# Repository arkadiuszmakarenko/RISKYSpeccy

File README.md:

# RISKY Speccy

A CH32V307 RISC-V cartridge that plugs into the ZX Spectrum edge connector
and provides:

- **Snapshot loader** — load `.z80` v1/v2/v3 files from USB storage and
  launch them with full register restore.
- **Tape player** — play `.tap` / `.tzx` files by injecting the EAR signal
  directly onto the data bus, compatible with the Spectrum's built-in tape
  loader.
- **Interface 2 ROM cart** — load `.rom` / `.bin` files (up to 16 KB) as an
  Interface 2 style cartridge ROM, mapped into the Spectrum's 0x0000-0x3FFF
  region.
- **On-screen UI** — full-screen file browser and VT100-compatible terminal
  rendered by the CH32 onto the ZX screen via the NMI mailbox, without any
  Z80 cooperation.

See [docs/](docs/) for architecture and subsystem documentation.

---

## Repository layout

```
board/          KiCad schematic and PCB design
docs/           Architecture and subsystem documentation
firmware/       CH32 firmware source
  Core/         WCH RISC-V core support files
  Debug/        UART debug driver
  Ld/           Linker script
  Peripheral/   CH32V30x peripheral drivers
  Startup/      Startup assembly
  User/         Application code (main subsystems)
  zx_src/       Z80-side cart ROM firmware (SDCC)
Makefile        Root build file (builds everything)
```

---

## Building

### Prerequisites

**CH32 RISC-V toolchain** (WCH GCC 12):

Download from [MounRiver Studio](http://www.mounriver.com/) or extract the
standalone toolchain archive.  The default path expected by the Makefile is:

```
~/RISC-V_Embedded_GCC12
```

**Z80 toolchain** (for the `zx_src` sub-firmware):

```
sudo apt install sdcc
```

The `sdasz80` assembler is included with SDCC.  GNU `objcopy`, `od`, and
`awk` must also be available (standard on most Linux systems).

### Build

```sh
make
```

Override the toolchain path if needed:

```sh
make TOOLCHAIN_DIR=/path/to/RISC-V_Embedded_GCC12
```

Useful targets:

```sh
make help                # full list of targets
make build-all-versions  # bootloader + both app variants + combined image
make versions            # show all output artifact paths
make clean
```

Build outputs land in `build/`.

### Continuous integration (GitHub Actions)

A workflow at [`.github/workflows/build.yml`](.github/workflows/build.yml)
builds the firmware on every push, pull request, tag, and manual dispatch.
It:

- installs the WCH RISC-V toolchain (V2.10) and SDCC from `apt`
- runs `make` at the repo root
- verifies that all expected artifacts (`Bootloader.bin`, `RISKYSpeccy.bin`,
  `RISKYZXS.UPD`, `RISKYZXS_COMBINED.bin`) are produced
- checks that the bootloader and app-update binaries fit their respective
  flash regions
- uploads the binaries as a workflow artifact
  (`RISKYZXSpectrum-firmware`, retained for 90 days) and the listings/maps
  as a separate logs artifact
- on tag pushes (`v*`) and on `release` events, attaches the user-facing
  binaries (`*.bin` / `*.UPD` at the top of `build/`) to a GitHub Release

The default `latest` release is marked as prerelease and is updated on
every non-PR run; tagged builds (`v1.2.3`, etc.) become stable releases.
No secrets are required — the workflow uses the default `GITHUB_TOKEN`
to create/update releases.

### Flashing options

| Mode | Command | Output | When to use |
|------|---------|--------|-------------|
| **Combined** (default) | `make flash` | `build/RISKYZXS_COMBINED.bin` | Fresh cartridge setup or bootloader + app in one shot |
| **Standalone (no BL)** | `make flash-standalone` | `build/RISKYSpeccy.bin` | Development or single-firmware deployment |
| **Bootloader only** | `make flash-bootloader` | `build/bootloader/Bootloader.bin` | Bootloader maintenance / recovery |
| **App via USB** | _(copy to USB drive)_ | `build/RISKYZXS.UPD` | After bootloader is installed |

The Linux `make flash*` targets drive a **WCH-LinkE** via OpenOCD.

#### Programming on Windows with WCH tools

1. Install [WCHISPTool](https://www.wch.cn/downloads/WCHISPTool_Setup_exe.html)
   and the **WCH-LinkE** USB driver (WCH provides a signed INF/VCP driver
   bundle — let the installer do it, or grab the driver from the
   MounRiver Studio distribution).
2. Connect the **WCH-LinkE** to the cartridge's SWD header (SWDIO / SWCLK /
   GND).  Power the Spectrum so the CH32V307 is alive on the edge connector.
3. Launch **WCHISPTool** and pick the chip family **CH32V30x** (the
   CH32V307 lives in this group).
4. In the device list, select the WCH-LinkE you just plugged in.  The tool
   should show the chip's `Device ID` once it talks to the target.
5. Click **...** next to the file box and point it at the build output:
   - `build/RISKYZXS_COMBINED.bin` — bootloader + application in one shot
     (use the **.bin** image, not `.elf`/`.hex`)
   - `build/RISKYSpeccy.bin` — application only (no bootloader)
   - `build/bootloader/Bootloader.bin` — bootloader only
6. Set the start address to **`0x08000000`** for any of the above.
7. Enable **"Erase before program"** and **"Verify after program"**, then
   click **Download** (or press F5).  Progress shows in the status bar;
   "Success" means programming finished and verified.

#### Updating the application via USB (no programmer)

For the **app-via-USB** path, the bootloader must already be installed on
the cartridge (use the WCHISPTool flow above once with the combined or
bootloader image to put it in place).

1. Copy `build/RISKYZXS.UPD` to the **root** of a **FAT12/FAT16/FAT32**
   formatted USB drive.
2. Insert the USB drive into the cartridge's USB port.
3. To **force IAP mode** (e.g. if the application is wedged and you want
   to reflash), fit a jumper across the **SWDIO / SWCLK** header pins
   before powering on.
4. Power on (or reset) the cartridge. The Ready LED should flash 3 times.
   The bootloader detects the drive and programs the application. If
   programming was successful, the Ready LED will flash slowly 10 times.
   If unsuccessful, it will start rapidly flashing.

See [docs/bootloader.md](docs/bootloader.md) for the full update flow,
state-machine details, and recovery options.

---

## CH32V303 RAM / FLASH split

The CH32V303 lets you trade FLASH for RAM (or vice versa) via the
**SRAM_CODE_MODE** field — bits `[7:6]` of the USER option byte at
`0x1FFFF802`.  The four available splits are:

| SRAM_CODE_MODE | FLASH  | RAM    |
|----------------|--------|--------|
| `00`           | 192 KB | 128 KB |
| `01`           | 224 KB |  96 KB |
| `10`           | 256 KB |  64 KB |
| `11`           | 288 KB |  32 KB |

This project uses **`00`** (192 KB FLASH + 128 KB RAM).  **You must set
this split before flashing the firmware**, otherwise RAM and FLASH regions
will not match the linker script and the firmware will not run.

### Setting the split with WCHISPTool (recommended)

This is the easiest method and requires only the WCH-LinkE programmer.

1. Open **WCHISPTool**, select chip family **CH32V30x**, and connect to the
   target (same as for flashing firmware — see [Flashing options](#flashing-options)).
2. Switch to the **Config** (or **Option Byte**) tab.
3. Locate the **SRAM_CODE_MODE** field (labelled `USER[7:6]` in some
   versions).
4. Select **`00`** from the drop-down to configure 192 KB FLASH + 128 KB RAM.
5. Click **Program** (or **Download**) to write the option byte.
6. Power-cycle or reset the board.  The new split is now active and you can
   proceed to flash the firmware.

### Setting the split with the Makefile (Linux + WCH-LinkE)

The repository provides Makefile targets that set the split and reboot the
chip in one step.  This is the quickest path on Linux.

| Command | Description |
|---------|-------------|
| `make split-info` | Read current option bytes (uses `minichlink -i`) |
| `make split-set` | Set the split to `MODE=0` (192K FLASH + 128K RAM) via minichlink |
| `make split-set MODE=0 SPLIT_TOOL=openocd` | Same, but uses OpenOCD |
| `make split-set-minichlink MODE=N` | Set split via minichlink, `N` = 0..3 |
| `make split-set-openocd MODE=N` | Set split via OpenOCD, `N` = 0..3 |

`MODE` values: `0` = 192K FLASH + 128K RAM, `1` = 224K + 96K, `2` = 256K + 64K,
`3` = 288K + 32K.  **This project requires `MODE=0`.**

```sh
# Default (recommended): mode 0 via minichlink
make split-set

# Mode 0 via OpenOCD
make split-set SPLIT_TOOL=openocd

# Power-cycle the board, then flash firmware
make flash
```

> After writing, power-cycle the board before flashing firmware.

### Setting the split with OpenOCD / WCH-LinkE on Linux (manual)

```sh
openocd -f interface/wch-riscv.cfg \
        -c "init; halt; \
            flash write_word 0x1FFFF802 0xC03F; \
            reset; exit"
```

The half-word `0xC03F` encodes USER byte `0x3F` (`SRAM_CODE_MODE = 00`,
all other bits at default) in the low byte and its complement `0xC0` in
the high byte, as required by the option byte format.

> After writing, power-cycle the board before flashing firmware.

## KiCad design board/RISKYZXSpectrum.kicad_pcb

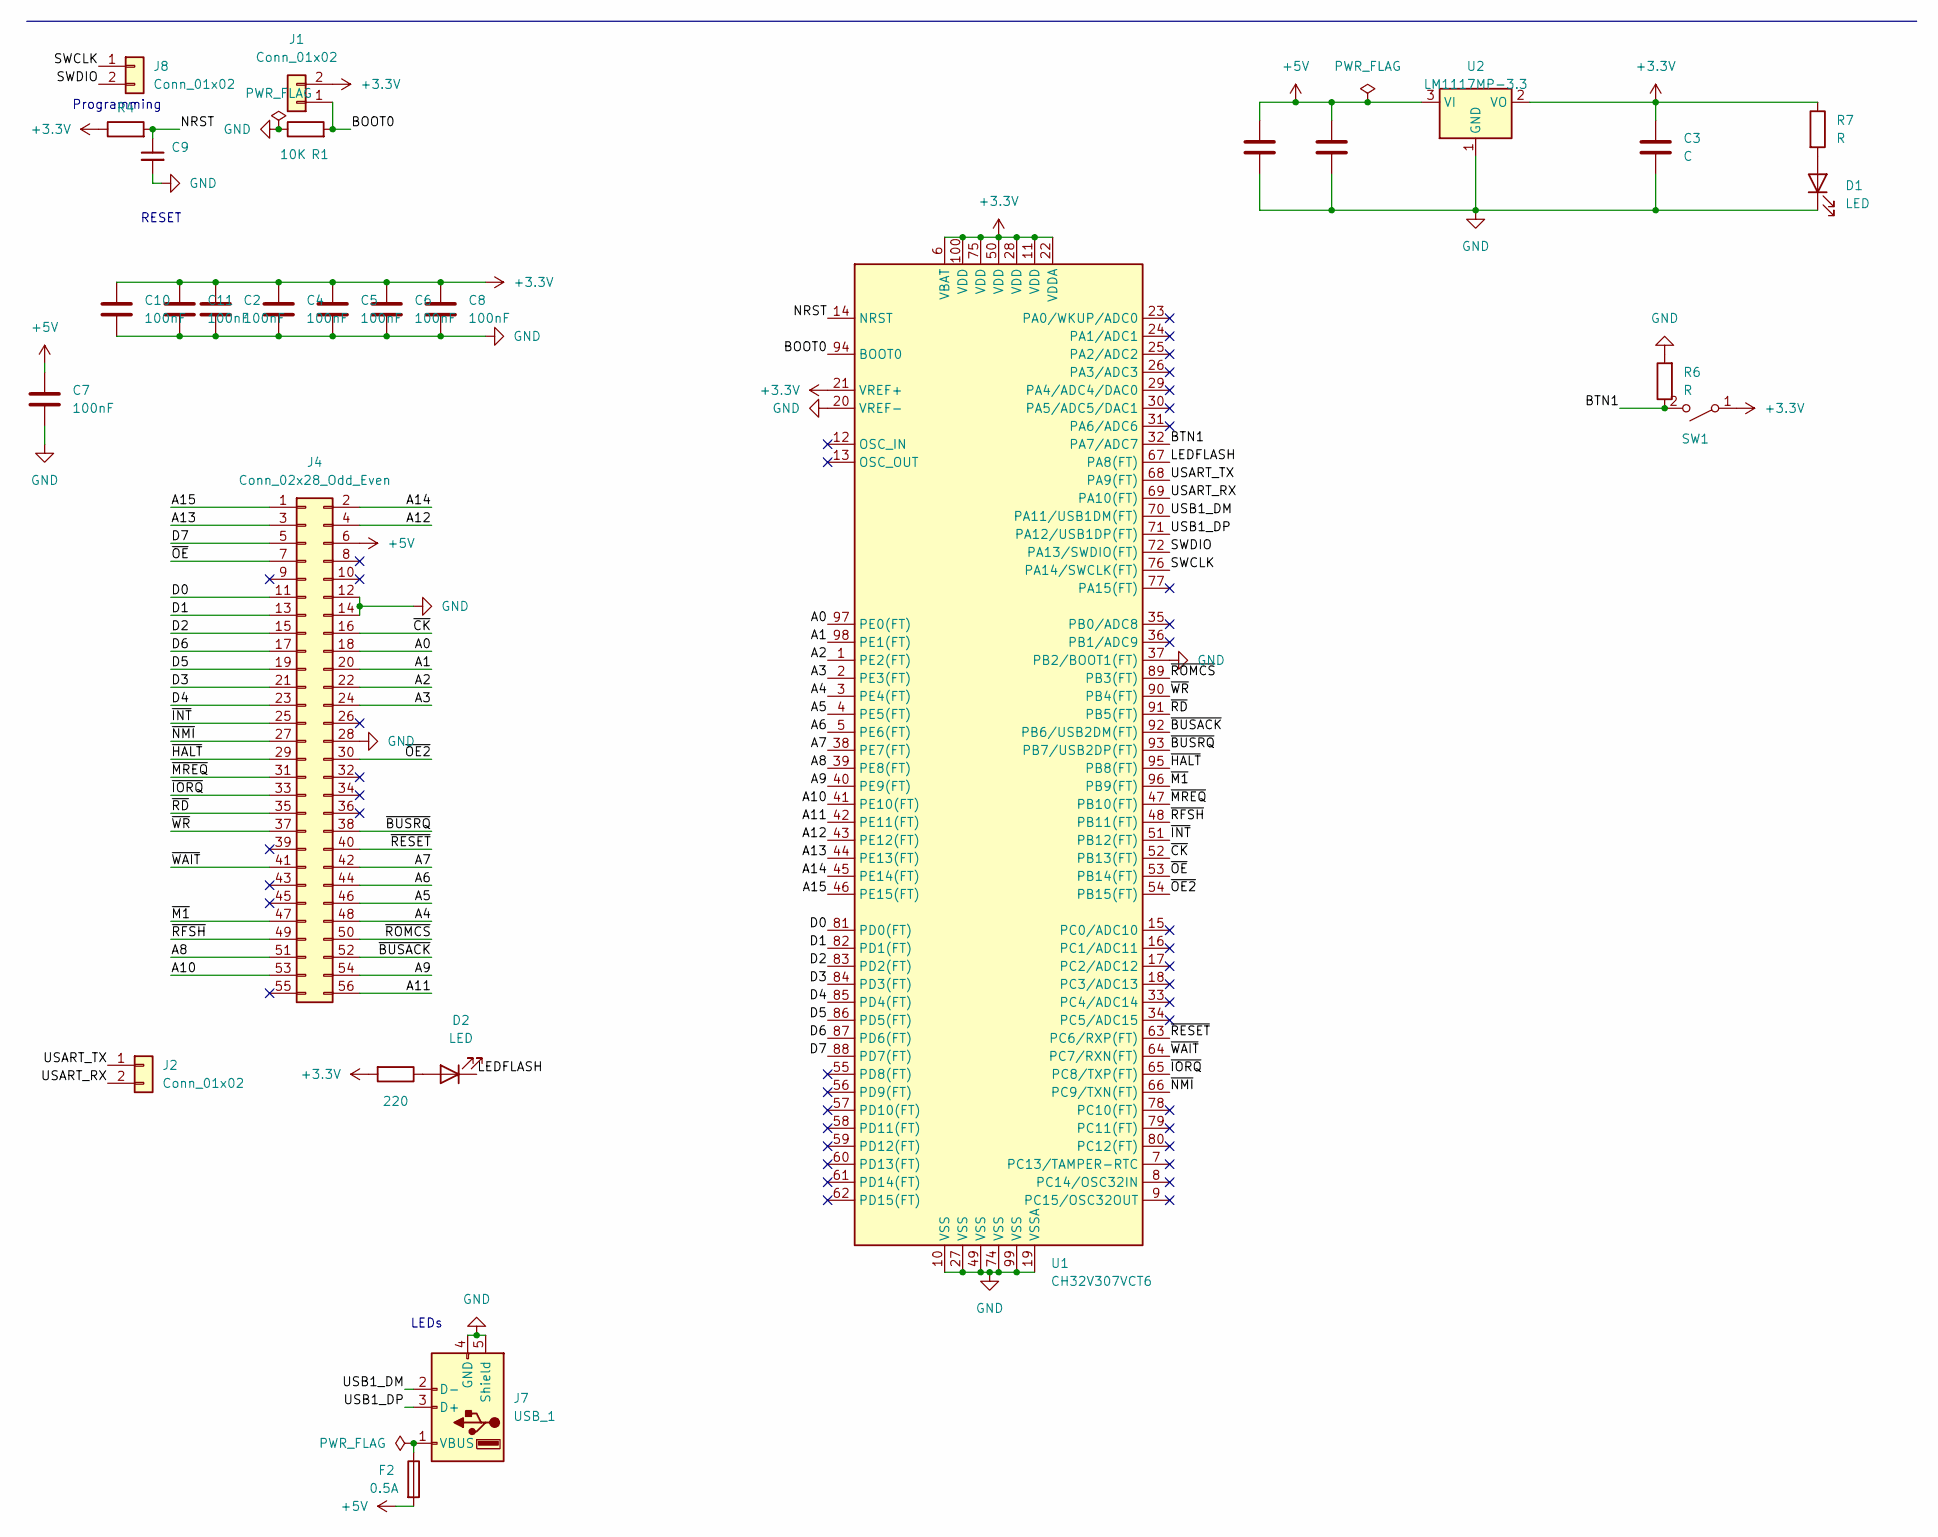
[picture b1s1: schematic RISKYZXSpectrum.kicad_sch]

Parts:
C1, C3, C12: C; C_0603_1608Metric_Pad1.08x0.95mm_HandSolder
C2, C4, C5, C6, C8, C10, C11: 100nF; C_0603_1608Metric_Pad1.08x0.95mm_HandSolder
C7: 100nF; C_1206_3216Metric_Pad1.33x1.80mm_HandSolder
C9: 100nF; C_0603_1608Metric_Pad1.08x0.95mm_HandSolder; LCSC C14663
D1, D2: LED; LED_0805_2012Metric_Pad1.15x1.40mm_HandSolder
F2: 0.5A; Fuse_1206_3216Metric_Pad1.42x1.75mm_HandSolder
J1, J2, J8: Conn_01x02; PinHeader_1x02_P2.54mm_Vertical
J4: Conn_02x28_Odd_Even; EdgeConnector_254x508x2x28_OddEven
J7: USB_1; USB_A_Connfly_DS1095
R1, R4: 10K; R_0603_1608Metric_Pad0.98x0.95mm_HandSolder
R5: 220; R_0603_1608Metric_Pad0.98x0.95mm_HandSolder
R6, R7: R; R_0603_1608Metric_Pad0.98x0.95mm_HandSolder
SW1: SW_SPST; SW_PUSH_6mm
U1: CH32V307VCT6; LQFP-100_14x14mm_P0.5mm
U2: LM1117MP-3.3; SOT-223-3_TabPin2

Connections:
+3.3V: C2.1, C3.1, C4.1, C5.1, C6.1, C8.1, C10.1, C11.1, J1.2, R4.1, R5.2, R7.1, SW1.1 (A), U1.6 (VBAT), U1.11 (VDD), U1.21 (VREF+), U1.22 (VDDA), U1.28 (VDD), U1.50 (VDD), U1.75 (VDD), U1.100 (VDD), U2.2 (VO)
+5V: C1.1, C7.1, C12.1, F2.2, J4.6, U2.3 (VI)
/A0: J4.18, U1.97 (PE0(FT))
/A1: J4.20, U1.98 (PE1(FT))
/A2: J4.22, U1.1 (PE2(FT))
/A3: J4.24, U1.2 (PE3(FT))
/A4: J4.48, U1.3 (PE4(FT))
/A5: J4.46, U1.4 (PE5(FT))
/A6: J4.44, U1.5 (PE6(FT))
/A7: J4.42, U1.38 (PE7(FT))
/A8: J4.51, U1.39 (PE8(FT))
/A9: J4.54, U1.40 (PE9(FT))
/A10: J4.53, U1.41 (PE10(FT))
/A11: J4.56, U1.42 (PE11(FT))
/A12: J4.4, U1.43 (PE12(FT))
/A13: J4.3, U1.44 (PE13(FT))
/A14: J4.2, U1.45 (PE14(FT))
/A15: J4.1, U1.46 (PE15(FT))
/BOOT0: J1.1, R1.2, U1.94 (BOOT0)
/BTN1: R6.1, SW1.2 (B), U1.32 (PA7/ADC7)
/D0: J4.11, U1.81 (PD0(FT))
/D1: J4.13, U1.82 (PD1(FT))
/D2: J4.15, U1.83 (PD2(FT))
/D3: J4.21, U1.84 (PD3(FT))
/D4: J4.23, U1.85 (PD4(FT))
/D5: J4.19, U1.86 (PD5(FT))
/D6: J4.17, U1.87 (PD6(FT))
/D7: J4.5, U1.88 (PD7(FT))
/LEDFLASH: D2.1 (K), U1.67 (PA8(FT))
/NRST: C9.1, R4.2, U1.14 (NRST)
/SWCLK: J8.1, U1.76 (PA14/SWCLK(FT))
/SWDIO: J8.2, U1.72 (PA13/SWDIO(FT))
/USART_RX: J2.2, U1.69 (PA10(FT))
/USART_TX: J2.1, U1.68 (PA9(FT))
/USB1_DM: J7.2 (D-_2), U1.70 (PA11/USB1DM(FT))
/USB1_DP: J7.3 (D+_3), U1.71 (PA12/USB1DP(FT))
/~BUSACK: J4.52, U1.92 (PB6/USB2DM(FT))
/~BUSRQ: J4.38, U1.93 (PB7/USB2DP(FT))
/~CK: J4.16, U1.52 (PB13(FT))
/~HALT: J4.29, U1.95 (PB8(FT))
/~INT: J4.25, U1.51 (PB12(FT))
/~IORQ: J4.33, U1.65 (PC8/TXP(FT))
/~M1: J4.47, U1.96 (PB9(FT))
/~MREQ: J4.31, U1.47 (PB10(FT))
/~NMI: J4.27, U1.66 (PC9/TXN(FT))
/~OE2: J4.30, U1.54 (PB15(FT))
/~OE: J4.7, U1.53 (PB14(FT))
/~RD: J4.35, U1.91 (PB5(FT))
/~RESET: J4.40, U1.63 (PC6/RXP(FT))
/~RFSH: J4.49, U1.48 (PB11(FT))
/~ROMCS: J4.50, U1.89 (PB3(FT))
/~WAIT: J4.41, U1.64 (PC7/RXN(FT))
/~WR: J4.37, U1.90 (PB4(FT))
GND: C1.2, C2.2, C3.2, C4.2, C5.2, C6.2, C7.2, C8.2, C9.2, C10.2, C11.2, C12.2, D1.1 (K), J4.12, J4.14, J4.28, J7.4 (GND_4), J7.5 (Shield), J7.SH (Shield_5), R1.1, R6.2, U1.10 (VSS), U1.19 (VSSA), U1.20 (VREF-), U1.27 (VSS), U1.37 (PB2/BOOT1(FT)), U1.49 (VSS), U1.74 (VSS), U1.99 (VSS), U2.1 (GND)
unnamed: D1.2 (A), R7.2
unnamed: D2.2 (A), R5.1
unnamed: F2.1, J7.1 (VBUS_1)

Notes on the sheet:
RESET
Programming
LEDs

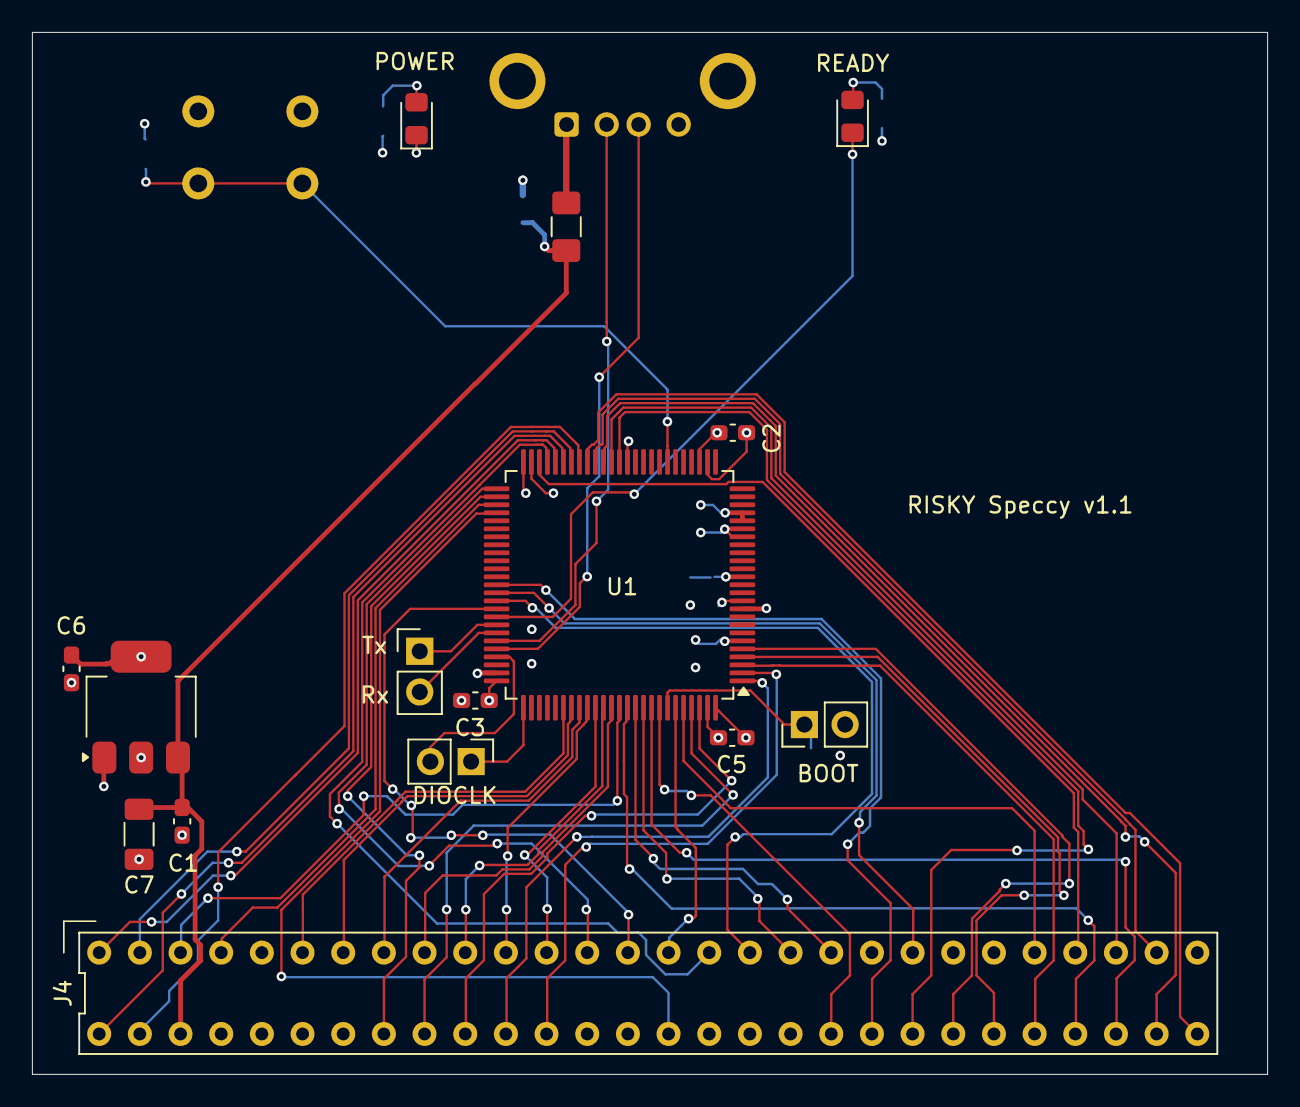
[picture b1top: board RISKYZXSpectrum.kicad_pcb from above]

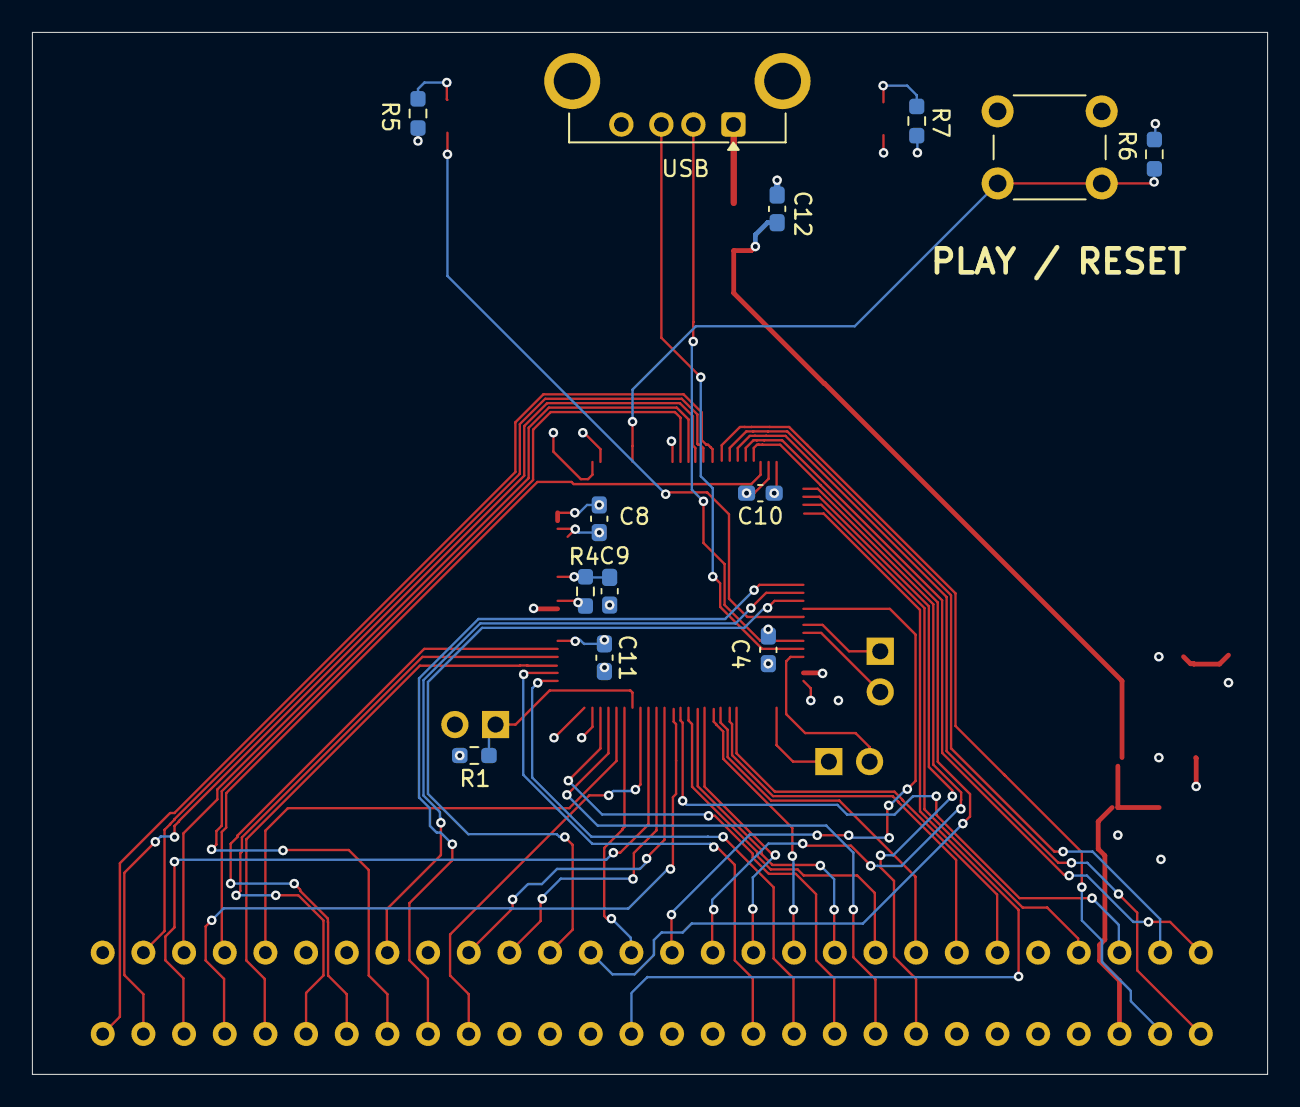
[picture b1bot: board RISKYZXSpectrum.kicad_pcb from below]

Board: 4 copper layers, 77.1 x 65.1 mm, 28 parts (13 on the bottom side), 57 nets.

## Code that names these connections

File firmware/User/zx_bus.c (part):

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// GPIOE Pins    0 - 16      Address
// GPIOD Pins    0 - 8       Data

// GPIOB Pin     3           ROMCS  0x0008
// GPIOB Pin     4           WR     0x0010
// GPIOB Pin     5           RD     0x0020

// GPIOB Pin     6           BUSACK 0x0040
// GPIOB Pin     7           BUSREQ 0x0080
// GPIOB Pin     8           HALT   0x0100

// GPIOB Pin     9           M1    0x0200
// GPIOB Pin     10          MREQ  0x0400
// GPIOB Pin     11          RESH  0x0800
// GPIOB Pin     12          INT
// GPIOB Pin     13          CK

// GPIOC Pin     6           RESET 0x0040
// GPIOC Pin     7           WAIT  0x0080
// GPIOC Pin     8           IORQ  0x0100
// GPIOC Pin     9           BDIR  0x0200

#pragma GCC push_options
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 * disabled) — after a successful ZX_LaunchZ80 handover or an explicit
 * ZX_RomcsRelease().  Cleared when the cart re-asserts control via
 * ZX_RomcsAssert() or ZX_BecomeInterface2().  Used by
 * ZX_HandleExternalResetIfAny() to decide whether a PC6 falling edge is
 * meaningful (the user pressed the ZX hardware reset button while we were
 * spun out). */
static uint8_t s_cart_released = 0u;
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               selection for 0x0000-0x3FFF; RAM at 0x4000+ is unaffected. */
            if (address == sp->handover_addr) {
                sp->handover_addr = 0xFFFFu;
                /* ROMCS (PB3) → input-floating: bits [15:12] of CFGLR.
                   CNF=01 (floating input), MODE=00.  One write; no RMW hazard
                   since the Z80 RD has already been released above. */
                GPIOB->CFGLR = (GPIOB->CFGLR & ~(0xFu << 12)) | (0x4u << 12);
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                /* Cart is now released: the Z80 is running game code from
                 * ZX RAM, ROMCS is floating, the ISR is masked.  Mark the
                 * state so ZX_HandleExternalResetIfAny() will react to a
                 * PC6 falling edge (ZX hardware reset) by re-engaging. */
                s_cart_released = 1u;
            }
        }
    } else {
        while (((GPIOB->INDR & sp->PinMREQ) == 0u) && ((GPIOB->INDR & sp->PinWR) != 0u)) { }

        if (((GPIOB->INDR & sp->PinMREQ) == 0u) && ((GPIOB->INDR & sp->PinWR) == 0u)) { // Check for delayed WR while MREQ remains active
            if ((address >= sp->RamBase) && (address <= sp->RomLast)) {
                GPIOD->CFGLR = sp->BusOff; // Data bus must be input while capturing host writes
                do {
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    }
    NVIC_DisableIRQ (EXTI15_10_IRQn);
    EXTI->INTENR &= ~EXTI_Line10;
    /* ROMCS (PB3) → input-floating: CFGLR bits [15:12], CNF=01 MODE=00. */
    GPIOB->CFGLR = (GPIOB->CFGLR & ~(0xFu << 12)) | (0x4u << 12);
    /* External-bus OE drivers (PB14, PB15) → input-floating, otherwise the
       cart keeps fighting the ZX ULA for the bus even after ROMCS is gone.
       CFGHR bits [27:24] = PB14, [31:28] = PB15.  CNF=01 MODE=00 each. */
    GPIOB->CFGHR = (GPIOB->CFGHR & ~((0xFu << 24) | (0xFu << 28)))
                 |  ((0x4u << 24) | (0x4u << 28));
    /* Cart released: arm external-reset detection for any post-release
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    ZX_AddrBusInput();
    ZX_DataBusInput();
    ZX_CtrlLinesInput();
    /* Re-drive ROMCS (PB3) and the external-bus OE buffers (PB14, PB15)
       as push-pull HIGH so the cart wins the bus again — mirrors the
       tristate done in ZX_RomcsRelease. */
    gpio.GPIO_Pin = ZX_PIN_ROMCS | GPIO_Pin_14 | GPIO_Pin_15;
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}

/* Detect a hardware reset of the ZX Spectrum asserted via the /RESET line
 * wired to PC6.  Intended to be polled from any context that needs to know
 * the user pressed the ZX hardware reset button — terminal idle loops (so
 * the screen can be redrawn after zxprog clears it), and post-launch spin
 * loops (so the cart can be re-engaged).
 *
 * Detection model: PC6 is configured as input pull-up after ZX_Z80Reset()
 * (or as OD output released HIGH), so idle reads HIGH.  A falling edge (LOW)
 * that persists past a 20 ms debounce window is treated as a real reset.
 * We then wait for the line to come back HIGH (button released) before
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
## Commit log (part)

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2026-03-22 Initial PCB
2026-04-19 Initial working device as EPROM with random game
2026-04-21 Add ZX Spectrum firmware source files and build system
    - Created Makefile for building ZX Spectrum firmware with Z88DK.
    - Added bin2zximage.py script to convert binary files to C source format.
    - Implemented patch_nmi_vector.py to modify the NMI vector in the binary.
    - Introduced zx.h header file defining memory map and color attributes.
    - Developed zxprog.c as the main firmware program, handling NMI and displaying "Hello World!" on the ZX Spectrum.
2026-04-22 memory monitor
2026-04-22 update makefile
2026-04-30 busreq
2026-05-01 improvement 2
2026-05-05 tap support
2026-05-06 z80 info page
2026-05-07 Add documentation for CH32–ZX Spectrum bus interface and ZX terminal UI
    - Created `zx_bus.md` to detail the hardware connections, ISR operation, and higher-level bus functions for the CH32V307 cartridge MCU interfacing with the ZX Spectrum.
    - Created `zx_terminal.md` to explain the architecture of the `zx_terminal` UI layer, including screen rendering, virtual terminal functionality, file browser operations, and bridge text handling.
    - Updated firmware version to v1.0.0 in `version.h`.
2026-05-07 Rename project from RISKYZXSpectrum to RISKYSpeccy in README
2026-05-07 Remove firmware version from README
    Removed current firmware version information from README.
2026-05-09 PCB udpate
2026-05-10 Custom bootloader to allow upgrade of the firmware from USB.
2026-05-10 Refactor GPIO initialization for IAP mode detection and update bootloader documentation
2026-05-10 tidy up
2026-05-10 tidy up hitory kiCad
2026-05-10 Stop tracking board/.history
2026-05-26 bugifxes with bootloader
2026-05-26 Add Interface 2 cartridge support with ROM loading functionality
2026-05-26 makfile update
2026-06-03 Update PCB job file and firmware for ROMCS handling - Updated the PCB job file version from 10.0.1 to 10.0.3 and adjusted the creation date. - Modified the RunCartWithRAM function to configure GPIO s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
2026-06-07 Refactor bootloader and documentation for clarity and functionality improvements
    - Adjusted LED blink count in main bootloader loop for better user feedback.
    - Enhanced Makefile with new split configuration commands and documentation.
    - Updated README with clearer instructions on build outputs and flashing options.
    - Improved bootloader documentation to clarify flash limits and application linker script.
    - Added detailed bus architecture diagram and explanations in zx_bus.md.
    - Clarified shared mailbox usage in zx_terminal.md and z80_launch_mechanism.md.
2026-06-18 ZX Spectrum Reset fix
2026-06-19 USB handling fixes and READY LED support
2026-06-19 ZX Spectrum Reset bugfix. Now cart performs full internal reset at zx spectrum reset or long press after loading z80
2026-06-23 Refactor minichlink SRAM_CODE_MODE handling for improved reliablility
2026-06-23 Github Actions
2026-06-23 Build fixes
2026-06-23 Fix toolchain path handling by creating a symlink to avoid issues with spaces in directory names
2026-06-23 bugixes
2026-06-23 Trigger CI on v0.2 pushes
2026-06-23 Update build workflow to include v0.2 branch for push and pull request events
2026-06-23 missing space in yaml file
2026-06-23 Refine release asset collection in build workflow to exclude unnecessary files and handle paths with spaces
2026-06-24 Add unsupported file format error handling to ZX terminal
2026-06-24 Add Interface 2 ROM cart feature description to README
2026-06-24 Refine GitHub Release handling to ensure 'latest' is not marked as prerelease
